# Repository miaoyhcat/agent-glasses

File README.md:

# CodexGlasses

**戴上它去公园散步。家里那台电脑，会替你把活干完。**

出门前说一句「检查一下那个项目，顺手把测试跑了」，话就落到了你电脑上的
Codex 或 DSH 手里。它只在你授权的那份项目副本上动，原件不碰。
你沿着湖边走一圈，抬眼看看镜片：连上电脑了、在读代码、跑到第 3 个测试、
卡在哪儿——不用回屋，也不用盯终端。走回来的时候，结果已经在镜片上了。

> **本项目仅允许个人非商业学习、研究、修改及自用。未经著作权人事先书面许可，严禁将本项目原创成果用于商业用途，包括商业销售、生产销售、商业集成、商业授权或其他以商业利益为目的的使用。违者必究。**
>
> **商业授权联系邮箱：3277681859@qq.com** · [个人自用与商业授权](COMMERCIAL-LICENSE.md) · [完整许可证](LICENSE)

[English](README_EN.md) · [产品对比](docs/product-comparison.md) · [设计图与资料总索引](docs/design-index.md) · [使用指南](docs/user-guide.md) · [验证记录](docs/verification-report.md)

CodexGlasses 是一套面向开发者的智能眼镜平台。它把眼镜端固件、Android 应用、
可自托管的桌面连接器、共享协议和硬件设计资料放进同一个仓库，
围绕「说出需求、批准任务、查看真实进度、接收结果」组织交互。

## 一次散步，四件事

| 你在做什么 | 眼镜在做什么 | 家里那台电脑在做什么 |
|---|---|---|
| 出门前说一句话 | 语音转写，上行 | 等你在本机点一下批准 |
| 沿着湖边走 | 显示「已连接 · 哪个项目 · 进行到哪一步」 | 在项目副本上跑 inspect / fix / test |
| 停下来看看 | 事件逐条上屏：读文件、跑测试、哪条没过 | 真实输出，不是「正在思考」的转圈 |
| 走回家 | 结果和验收状态 | 留档，下次接着来 |

需要批准的地方，现在可以说一句「批准」——回屋点那一下当然也行。语音批准默认是关的，要在电脑端配置里打开；口令认不出来就当没听见，任务原地不动。

## 接哪些 Agent：Codex 与 DSH

两类 agent 走同一条链路：**眼镜 → 手机 → 电脑连接器 → 隔离 worker → agent CLI**。
模型密钥留在电脑端，任务进度取自真实会话事件，容器里没有外网。

| Agent | 怎么接 | 现在的状态 |
|---|---|---|
| **Codex**（官方 App Server） | 官方 JSONL stdio 塞进无外网 Docker worker | 按实测 0.162.1 的 schema 接入；环境初始化和配置读取可用，`thread/start` 未完成（详见[接入说明](agent-integration/codex/README.md)） |
| **DSH**（DeepSeek Harness） | 同一个 worker，换一条命令行即可 | 入口已留好（`CODEXGLASSES_AGENT` / `CODEXGLASSES_AGENT_ARGS`），**未在真实 DSH 上实测**（详见[DSH 接入](agent-integration/dsh/README.md)） |

换 agent 不用改代码：

```bash
# 默认就是 Codex，不设这两个变量行为不变
CODEXGLASSES_AGENT=dsh \
CODEXGLASSES_AGENT_ARGS="<DSH 的等价启动参数>" \
python3 agent-integration/codex/worker_entry.py
```

前提写在 [DSH 接入说明](agent-integration/dsh/README.md) 里：worker 按「一行一个 JSON 帧」
转发，DSH 侧协议不同就得加一层适配；模型请求要能指向本机 broker（`127.0.0.1:9041`）。
没跑过的东西就是没跑过，不写成「已适配」。

## 欢迎 issue 和 star

这是个人项目，但有人在用、有人较真，它才会变好。

- **跑不通、发现漏洞**：提 [issue](https://github.com/miaoyhcat/codex-glasses/issues/new/choose)，
  写清系统、Python 版本、你执行到哪一步、报了什么错。能复现的最有价值。
- **想要的功能**：也提 issue，说清你实际想解决什么事，而不是「加个 X」。
- **觉得有点意思**：点个 [star](https://github.com/miaoyhcat/codex-glasses)——
  这是最直接的反馈，让我知道还有人在看。

许可仍然只开放个人非商业使用，商业用途请先联系。

## 为什么是 CodexGlasses

| 核心特色 | 用途 | 仓库入口 |
|---|---|---|
| **随身开发任务入口** | 检查项目、修复问题、运行测试；显示连接电脑、项目、任务阶段与结果 | [Codex 接入](agent-integration/codex/README.md) · [DSH 接入](agent-integration/dsh/README.md) |
| **面向信息的HUD** | 时间、通知、转写、AI文字与任务状态；手机完成中文栅格化 | [固件与HUD](firmware/README.md) |
| **采集与本地缓存** | 摄像、短录像、录音、媒体校验、确认后删除及断点上传 | [固件](firmware/) / [手机](mobile/README.md) |
| **自己掌握连接器** | 设备绑定、证书核验、项目授权、本机审批及日志事件 | [桌面端](desktop/codexglasses/) / [协议](agent-integration/protocols/protocol.md) |
| **从设计到代码可审查** | KiCad、STEP/STL、OpenSCAD、BOM、装配资料、测试与演示 | [设计总索引](docs/design-index.md) |

## 看见并控制真实任务

“检查这个项目有没有Bug” → 选择授权电脑和项目 → 电脑本机批准 → 智能体工作 → HUD显示实际事件和结果。后续fix/test任务可关联会话，取消与断线恢复有明确状态。

```mermaid
flowchart TD
  G["眼镜：显示 / 采集 / 缓存"] <--> P["Android：语音 / 媒体 / 网络"]
  P <--> D["桌面连接器：身份 / 授权 / 事件"]
  D <--> C["官方 Codex App Server"]
  C --> W["授权项目副本与测试"]
  W --> D
```

模型密钥留在电脑端，任务进度取自可获取的会话事件。回合完成与独立测试验收分别记录。[架构说明](docs/architecture.md)与[安全设计](SECURITY.md)提供具体实现。

## 与市面上产品相比，聚焦在哪里

| 产品 | 核心定位 | 公开显示/交互特点 |
|---|---|---|
| **CodexGlasses** | 可审查、可自托管的智能体眼镜平台 | H1单目HUD设计；P1近眼显示适配；自有项目上的inspect/fix/test、真实任务事件与本机审批 |
| **Ray-Ban Meta Gen 3** | 日常拍摄与语音AI | Camera + Audio型号；第一视角记录、通话与日常助手 |
| **Meta Ray-Ban Display** | 带镜片显示的消费AI眼镜 | 单目全彩600×600；消息、字幕、导航与腕带交互 |
| **Rokid Glasses with Display** | 轻量翻译与信息显示 | MicroLED、30°FOV；字幕、翻译、提词与拍摄 |
| **Even Realities G2** | 字幕与信息辅助 | 双目绿光640×350、27.5°FOV；轻量信息提示、沟通辅助 |
| **Brilliant Halo** | 可编程AI眼镜 | 彩色近眼显示；可编程应用与个人AI体验 |
| **XREAL One Pro** | 空间大屏与外部主机显示 | MicroOLED、57°FOV；电脑/游戏/移动设备大屏 |
| **RayNeo X3 Pro** | 全彩AI与空间AR | 双目全彩640×480、30°FOV；导航、翻译、空间应用 |

对比公开定位与接口；厂商规格、项目设计预算和软件验证分别注明。完整来源、参数口径及可机读表见[产品比较](docs/product-comparison.md)。

## 两条硬件路径，一套软件链路

| 配置 | 用途与资料 |
|---|---|
| H1 | 集成镜架的光学、结构、质量和功耗设计；[结构CAD](hardware/mechanical/) / [光学](hardware/optics/) / [预算](hardware/power/) |
| D0 + P1 | D0提供摄像/音频/缓存开发台架；P1使用T-Glass V2近眼显示设备；[接线](hardware/assembly/d0-wiring.csv) / [P1显示](hardware/optics/p1-tglass-v2.md) |

参数按用途给出：H1的66.45g与定义混合负载8.486h是工程预算；P1显示配置单独记录。对应输入、测试范围和证据在[验证报告](docs/verification-report.md)及[证据索引](docs/evidence-index.json)。

## 快速运行

```bash
python -m venv .venv
# 激活虚拟环境后：
python -m pip install -e .
python simulator/demo.py
python scripts/verify.py
```

演示使用真实本机HTTPS完成绑定、审批、任务事件及媒体传输，智能体标注SIMULATOR。公开样例的真实Codex/本地模型复现见[本地模型实验](agent-integration/codex/local-benchmark.md)。

```bash
codexglasses --state runtime init --host 电脑私网IP --name 我的开发电脑
codexglasses --state runtime project-add demo examples/demo-project --allow-snapshot-writes
codexglasses --state runtime serve --simulate
```

Android调试APK与Python wheel位于[releases](releases/README.md)。固件构建入口：`python scripts/build_firmware.py`；Android构建入口：`python scripts/build_android.py --sdk 官方SDK目录`。

## 从这里找到全部资料

- [设计、原理图、PCB、CAD与BOM总索引](docs/design-index.md)
- [产品需求](docs/product-requirements.md) / [架构比较](docs/architecture.md) / [工程计算](docs/feasibility-study.md)
- [市场研究：16款产品](docs/market-research.md) / [产品对比](docs/product-comparison.md) / [资料来源](docs/sources.md)
- [装配与制造资料](docs/manufacturing-guide.md) / [使用指南](docs/user-guide.md)
- [测试记录](docs/verification-report.md) / [38项验收用例](docs/acceptance-matrix.csv) / [安全设计](SECURITY.md)
- [修改与贡献](CONTRIBUTING.md) / [更新记录](CHANGELOG.md) / [GitHub发布说明](scripts/publish-github.md)

本次公开源码发布沿用v0.2软件与固件版本。已有记录包括62项主机测试、API26模拟器运行、两个固件目标交叉编译与公开样例的真实模型修复；证据均保留原执行日期和范围。

原创材料采用**个人非商业源代码可查看许可证**。第三方条款保留，见[NOTICE.md](NOTICE.md)。商业合作请联系 **3277681859@qq.com**。

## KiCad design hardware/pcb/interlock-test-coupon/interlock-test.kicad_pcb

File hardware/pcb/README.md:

# PCB交付范围

仅提供原创3.3V LED窗口联锁测试coupon的KiCad源文件、网络连接CSV及可再生脚本；它不是H1整机主板。H1的电源、光机、RF、充电、存储、音频、FPC尚未整合为可投板资料。

测试板有18个器件位、10个网络，已做KiCad复读和DRC。完整结果以`docs/evidence/interlock-drc.txt`为准；元数据警告未隐去。生成脚本依赖KiCad7的pcbnew，运行后须导出网表并与实际板文件连接表核对。封装是自绘嵌入数据，仍需按选定器件独立核图，不能把DRC当作封装、电气或安全功能认证。

制造输出如位于`interlock-test-coupon/fabrication-review/`，只对应这个实验coupon，需工程师审核后才可作为离体测试板打样。没有H1主板Gerber、钢网、飞针测试或整机制造通过声明。

测试板逐件BOM位于`../bom/interlock-coupon.csv`，其MCP6547为DIP8的-I/P版本；SOIC的-I/SN不能焊到当前板。LED具体SKU/极性仍须独立核对。

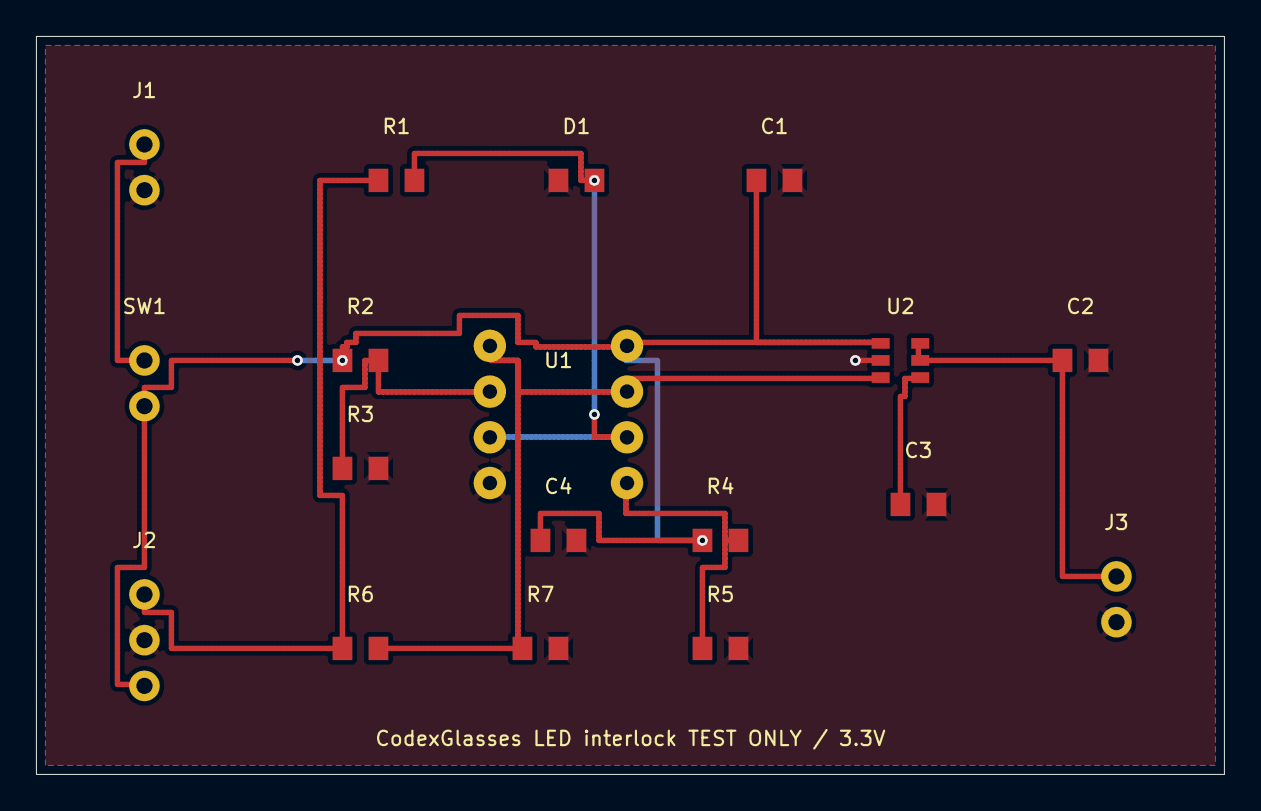
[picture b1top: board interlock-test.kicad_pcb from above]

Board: 2 copper layers, 66.0 x 41.0 mm, 18 parts (0 on the bottom side), 10 nets.

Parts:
C1, C2: 1uF
C3: 1nF
C4: 100nF
D1: VISIBLE_GREEN_LED
J1: 3V3_IN
J2: MCU_CTRL
J3: CAMERA_3V3_OUT
R1: 330
R2: 232k 1%
R3, R5: 100k 1%
R4: 22.1k 1%
R6: 10k
R7: 100k
SW1: EXTERNAL_MASTER_SWITCH
U1: MCP6547-I/P
U2: TPS22918DBVR

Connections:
CT: C3.1, U2.4
EN: R6.2, R7.1, U1.1, U1.7, U2.3
GND: C1.2, C2.2, C3.2, C4.2, D1.1, J1.2, J2.2, J3.2, R3.2, R5.2, R7.2, U1.4, U2.2
LED: D1.2, R1.2, U1.3, U1.6
REQ: J2.1, R1.1, R6.1
VCAM: C2.1, J3.1, U2.5, U2.6
VHIGH: R4.2, R5.1, U1.5
VIN: J1.1, SW1.1
VLOW: R2.2, R3.1, U1.2
VSW: C1.1, C4.1, J2.3, R2.1, R4.1, SW1.2, U1.8, U2.1
